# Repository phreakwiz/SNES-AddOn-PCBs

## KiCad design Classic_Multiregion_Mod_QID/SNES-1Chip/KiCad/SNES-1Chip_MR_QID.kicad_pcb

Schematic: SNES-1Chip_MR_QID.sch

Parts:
74*00, 74HCU04: 74XX-EU_SO14
74HC(T)125: 74HC125D; 74XX-EU_SO14
C1, C2, C3, C4, C5, C6, C7: C100n; SNESCART_Z0805
C8, C9, C10, C11: C22p; SNESCART_Z0805
CTRL1, CTRL2, CTRL3, CTRL4: WIREPAD_SMD1_27-2_54
IC1: 74HC27D; 74XX-EU_SO14
IC2: 74HC30D; 74XX-EU_SO14
L50, L60: WIREPAD_SMD1_27-2_54
MODE1: WIREPAD_SMD1_27-2_54
NTSC_21.477MHZ1: CRYSTAL_HC49UP
PAL_17.734MHZ1: CRYSTAL_HC49UP
R1: R10k; SNESCART_Z0805
R2, R3: R220; SNESCART_Z0805
R4, R5: R330; SNESCART_Z0805
R6, R7: R1M; SNESCART_Z0805
RES-IN1: WIREPAD_SMD1_27-2_54
RES-OUT1: WIREPAD_SMD1_27-2_54
SRGB9: WIREPAD_SMD1_27-2_54
U$1, U$4, U$5: MY_JUMPER; SNESCART_MYJUMP
U$2, U$3: PIC16F630_SIMPLE; SNESCART_PIC16F630
U$6: SNESCART_CONN_SPARSE; SNES_DIV_SNESCART_CONN_SPARSE
X1: WIREPAD_SMD1_27-2_54

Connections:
/N$2: 74HC(T)125.1 (OE), 74HC(T)125.4 (OE), 74HC(T)125.10 (OE), 74HC(T)125.13 (OE), IC2.8 (O)
/N$4: IC2.3 (I2), U$6.61 (PA5)
/N$5: IC2.2 (I1), U$6.60 (PA3)
/N$6: IC1.3 (I0), U$6.4 (/PARD)
/N$7: IC1.4 (I1), U$6.3 (PA6)
/N$8: IC1.6 (O), IC2.11 (I6)
/N$9: IC2.6 (I5), U$6.28 (PA0)
/N$10: R1.2, RES-IN1.1, U$2.13 (A0), U$3.2 (A5)
/N$11: L50.1, R2.2
/N$12: R2.1, U$3.5 (C5)
/N$13: R3.1, U$3.6 (C4)
/N$15: L60.1, R3.2
/N$16: IC1.5 (I2), U$6.34 (PA7)
/N$17: IC2.12 (I7), U$3.7 (C3)
/N$18: U$1.P$1 (1), U$6.56 (CIC_P6)
/N$19: U$2.5 (C5), U$3.10 (C0)
/N$20: IC2.1 (I0), U$6.59 (PA1)
/N$21: IC2.5 (I4), U$6.29 (PA2)
/N$22: IC2.4 (I3), U$6.30 (PA4)
/N$26: 74*00.12 (I0), 74HCU04.6 (O)
/N$27: 74HCU04.1 (I), C8.1, PAL_17.734MHZ1.1, R6.1
/N$28: 74HCU04.3 (I), C9.1, PAL_17.734MHZ1.2, R4.2, R6.2
/N$29: 74HCU04.13 (I), C10.1, NTSC_21.477MHZ1.1, R7.1
/N$31: 74*00.5 (I1), 74*00.8 (O)
/N$32: 74*00.4 (I0), 74*00.11 (O)
/N$33: CTRL2.1, U$3.11 (A2)
/N$34: CTRL3.1, U$3.12 (A1)
/N$35: 74*00.3 (O), 74*00.9 (I0)
/N$36: 74*00.6 (O), X1.1
/N$37: 74HCU04.2 (O), R4.1
/N$38: 74HCU04.4 (O), 74HCU04.5 (I)
/N$39: CTRL1.1, U$1.P$2 (2), U$2.2 (A5)
/N$41: 74*00.10 (I1), 74HCU04.8 (O)
/N$42: 74HC(T)125.3 (O), 74HC(T)125.6 (O), 74HC(T)125.8 (O), 74HC(T)125.11 (O), U$6.50 (D4)
/N$44: 74HCU04.9 (I), 74HCU04.10 (O)
/N$46: CTRL4.1, U$3.13 (A0)
/N$48: U$2.10 (C0), U$6.55 (CIC_P2)
/N$49: U$2.9 (C1), U$6.24 (CIC_P1)
/N$50: 74HCU04.12 (O), R5.1
/N$51: U$2.8 (C2), U$6.25 (CIC_P7)
/N$52: U$2.6 (C4), U$3.9 (C1)
/N$53: U$2.7 (C3), U$3.8 (C2), U$4.P$2 (2), U$5.P$2 (2)
/UIGR: 74HC(T)125.2 (I), 74HC(T)125.5 (I), 74HC(T)125.9 (I), 74HC(T)125.12 (I), U$2.3 (A4), U$3.4 (A3)
/VCC_2: 74HC(T)125.14 (VCC), C5.1, C6.1, C7.1, IC1.14 (VCC), IC2.14 (VCC), U$6.58 (VCC)
GND: 74*00.7 (GND), 74HC(T)125.7 (GND), 74HCU04.7 (GND), C1.2, C2.2, C3.2, C4.2, C5.2, C6.2, C7.2, C8.2, C9.2, C10.2, C11.2, IC1.1 (I0), IC1.2 (I1), IC1.7 (GND), IC1.9 (I0), IC1.10 (I1), IC1.13 (I2), IC2.7 (GND), R1.1, U$2.4 (A3), U$2.14 (GND), U$3.14 (GND), U$5.P$1 (1), U$6.5 (GND), U$6.36 (GND)
unnamed: IC1.8 (O), SRGB9.1
unnamed: RES-OUT1.1, U$2.11 (A2)
unnamed: 74*00.1 (I0), 74*00.2 (I1), 74*00.13 (I1), IC1.11 (I2), MODE1.1, U$3.3 (A4)
unnamed: 74HCU04.11 (I), C11.1, NTSC_21.477MHZ1.2, R5.2, R7.2
VCC: 74*00.14 (VCC), 74HCU04.14 (VCC), C1.1, C2.1, C3.1, C4.1, U$2.1 (VCC), U$3.1 (VCC), U$4.P$1 (1), U$6.27 (VCC)

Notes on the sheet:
PAL Quarz
NTSC Quarz

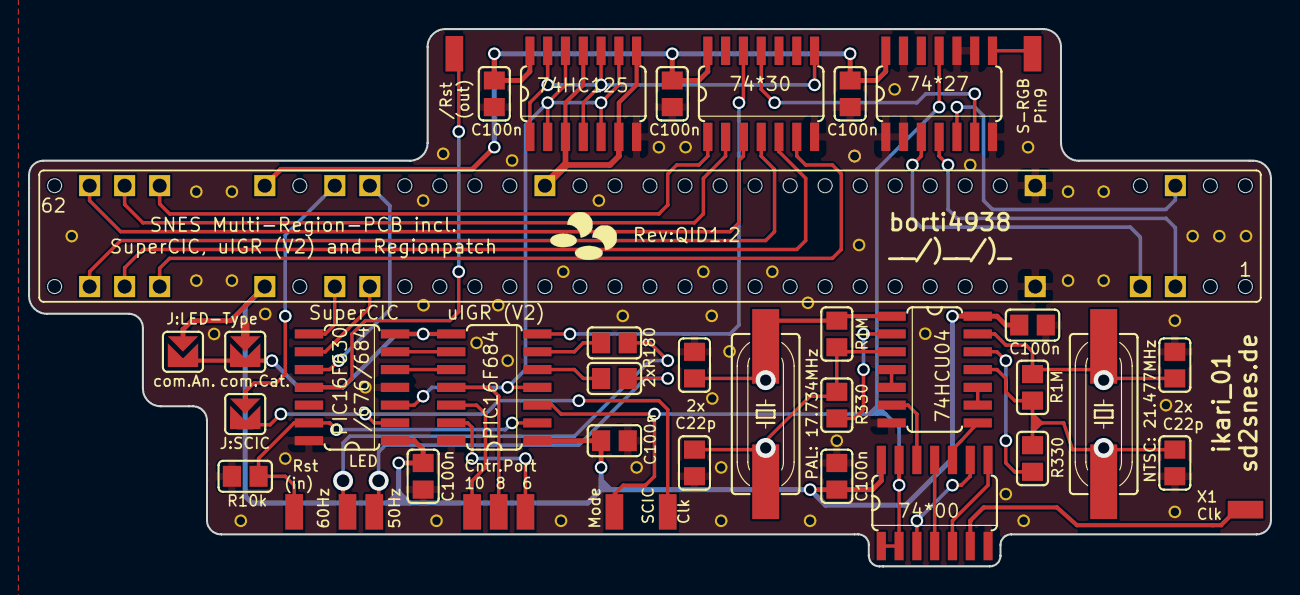
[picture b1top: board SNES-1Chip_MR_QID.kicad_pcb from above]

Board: 2 copper layers, 88.6 x 38.4 mm, 42 parts (0 on the bottom side), 50 nets.

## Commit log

2015-07-21 revert small typos
2015-08-06 New folder structure and improvements on the uIGR code
    Here are some notes out of my other repository:
    >>
    improved data sampling, combined code for with(out) lock option
    - data sampling on falling clock edge
    - last value taken right before the edge detection
    - support of third party controllers like micros UWRC(V2)
2015-08-07 Minor improvement I forgot about the SGB support. With the SGB specific controller reading the validity test fails if RAIF is cleared after the reading button B.
2015-08-26 Minor updates for the Logo-PCBs: - move resistors for LEDs to the LED PCB - LEDs can be either in 0805 or P-LCC-2 package
2015-09-23 Remove firmware folder and place download links instead It is easier for me to keep it up to date ;)
2015-09-25 Code Backup for ATTiny45
    - created by jensma 2012 (jensam.de)
    - ported to atmel studio by sanni 2013
    - modified by borti4938 2015
    Code runs best at 8MHz
    use code in *_on_* folder if you want the LEDs to be on after animation
    use code in *_off_* folder if you want the LEDs to be switched off after animation
2015-09-25 ready update
2015-10-15 Update Design: - minor changes and adjustments
2015-10-15 RGB Bypass Version Update: - adjustment of wires - mirrored positioning of R, G and B pad - exact values for resistors - add a version with CSYNC-buffering (for 1Chip03 boards and later) - more detai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
2015-10-16 README update
2015-10-26 Lib update: still nasty sorted and awful design (this will never change :P)
2015-11-04 correct a small error in README-file
2015-12-03 rename files
2015-12-03 Minor Updates: - Dual design for crystals (SNES-1Chip_MR_QID only); SMD and THT crystals are now supported (If THT crystals are used, SMD pads have to isolated, manually.) - minor tweaks of traces - 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
2015-12-18 Update: 330uF tantalum in CSYNC line at the output of the THS7374.
2016-02-01 Update silkscreen
2016-02-11 move R12 to avoid a slight overlapping between the PCB and a mounting screw in SNES Mini and SFC Jr.
2016-02-19 add part list for multi region boards in QID
2016-02-19 add a hint for using THT crystals
2016-02-20 update part list (fix issue #2)
2016-02-21 new folder structure
2016-02-21 introduce RGB-amp for the 3Chip-SNES (PAL models only) with a THS7314
2016-02-23 update tantal-cap sizes
2016-02-24 pictures for issue #3
2016-03-18 A user-note for the region patch
2016-04-22 update firmware text
2016-04-22 add thermals to ground pad (easier to solder) and reduce PCB size a bit
2016-04-22 add gerber files for MR QID
2016-04-22 rename folders a bit, add thermals to GND pads
2016-04-22 remove deprecated designs
2016-04-22 update design: move GND pad
2016-04-22 update libs
2016-10-18 Backup V3
2016-10-18 Initial commit V4
2016-11-07 Correct resistor values for brightness correction
2017-01-26 sd2snes to Rev.H Mod
2017-02-02 Clarify that setting HWID is an optional step
2017-02-13 go to version 4.1
2017-02-14 Change resistor values
2017-03-19 expression changed
2017-07-14 additional preparation step for Rev.G sd2snes
2017-11-17 Update README and BOM
2017-11-19 include some feedback. Thanks to shartqueefa (shmups forum user) for that :)
2017-11-20 some refinements on "brightness and ghosting issue" description
2017-11-23 clean up
2017-12-07 revert a small copy n paste error
2017-12-27 add LICENSE
2018-01-24 added missing KiCad files
2018-01-24 deleted backup files
2018-02-12 update digital audio mod incl a new no-cut design with coax
2018-02-14 PCB Update
2018-02-16 small bugfix in values (MPNs were right)
2018-02-23 SNES 1Chip replacement
2018-04-17 fix some bugs in BOM
2018-05-26 Minor typo bugfix. Thanks to Nope (twitter @Nohpuh)
2019-06-10 move classic multi-region mod
2019-06-15 update license
2019-06-16 initial commit multi region pcb with dejitter included
2019-06-17 add a header to readme
2019-06-17 general notes on installation and a common picture
2019-06-17 initial commit: SNS-CPU-RGB-01 installation
2019-06-17 typo removed
2019-06-19 rename folder of EAGLE gerber legacy format output (issue #7)
2019-06-19 some additional remarks
2019-06-19 installation guide for the PAL SNSP-CPU-1CHIP-01/02 mainboard
2019-07-23 add missing dfo gui files
2019-07-23 add missing installation step
2019-07-23 add installation guide for the SNN-CPU-01 (SNES2) mainboard
2019-08-13 add installation readme for SNSP-CPU-01 and SNSP-CPU-02 boards
2019-08-14 headline fixes
2019-08-14 Add description of C59 fix
2019-08-14 add installation guide SNS-CPU-APU-01
2019-08-14 pic update
2019-08-14 PCB update: - double /CS.i pad - color carrier generate inside CPLD (trace removed) - replace resistor arrays by simple components - add footprint for resistor from SNES mainboard to have resistor no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
2019-08-14 version typo removed
2019-10-29 clarification
2020-03-22 update PCB design: - selectable sync level for the buffered output - video buffer for sync instead of transistor
2020-03-25 update PCB design: - selectable sync level for the buffered output - video buffer for sync instead of transistor - color carrier fix applied - some GND between sub-carrier and master clock output
2020-03-30 change link from configuration file to compiled hex
